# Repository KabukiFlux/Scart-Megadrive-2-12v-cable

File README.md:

# Megadrive/Genesis 2 to Scart adapter with 12V

<b align="center">PCB form Megadrive/Genesis 2 RGB minidin to Scart adapter with 12V DCDC boost (4:3 switching)</b>

## Table of contents

- [Why](#why)
- [Description](#description)
- [Schematics](#schematics)
- [Install](#install)
- [Pics and final result](#pics-and-final-result)
- [Premade cables with minidin 9](#premade-cables-with-minidin-9)

## Why?

When we plug a Megadrive 2 console via scart on the "newer" CRT TVs as the minidin provides 5v on the console side the
tv will switch to AV with a 16:9 aspect ratio. We need to deliver between 9v to 12v on the swtiching side to output
directly to AV with 4:3 aspect ratio.

## Description

This is intended to be a PCB using the default Megadrive/Genesis 2 RGB cable schematic but adding the 12v DC-DC switching boost
on the scart side from the 5v supplied by the MD2.

This board intends to provide a standard Sega Megadrive 2 RGB cable (Sega Genesis).

In the BOM directory there's an interactive BOM with all the required components.

In the gerbers directory we have the gerbers to manufacture the boards.

In the KiCAD folder we can find the KiCAD project itself.

## Schematics

You can find a copy on PDF on the root of the repository.

## Install

1- Send to manufacture the GERBER board to JLCPCB or other PCB manufacturer.

2- Get the components required, you can see here the Bill Of Materials [BOM](ibom.html)

3- Solder the wire to each of the pads and to the scart male.

4- Remember to solder the shield of the scart to the GND as well to avoid noise issues.

### Pics and final result

At this stage you should have something like this:

## Premade cables with minidin 9

Of course you can always try to solder the minidin 9 connectors from Aliexpress, good luck with that!

(You will need good flux and scratch the surface - some of them are almost imposible)

But my recommendation is to buy these ones:

1- RS 75ohm cable with shield: [RS Spain link code 724-1150](https://es.rs-online.com/web/p/cables-din/7241150)

2- Minidin 9 male to male cable: [Aliexpress 3m male to male with shield](https://es.aliexpress.com/item/1005006201886253.html)

I'm not responsible
============
And yes, read below, no responsibility taken on bad use.

DISCLAIMER (See Licensing)
==========================
See LICENSE for more information.

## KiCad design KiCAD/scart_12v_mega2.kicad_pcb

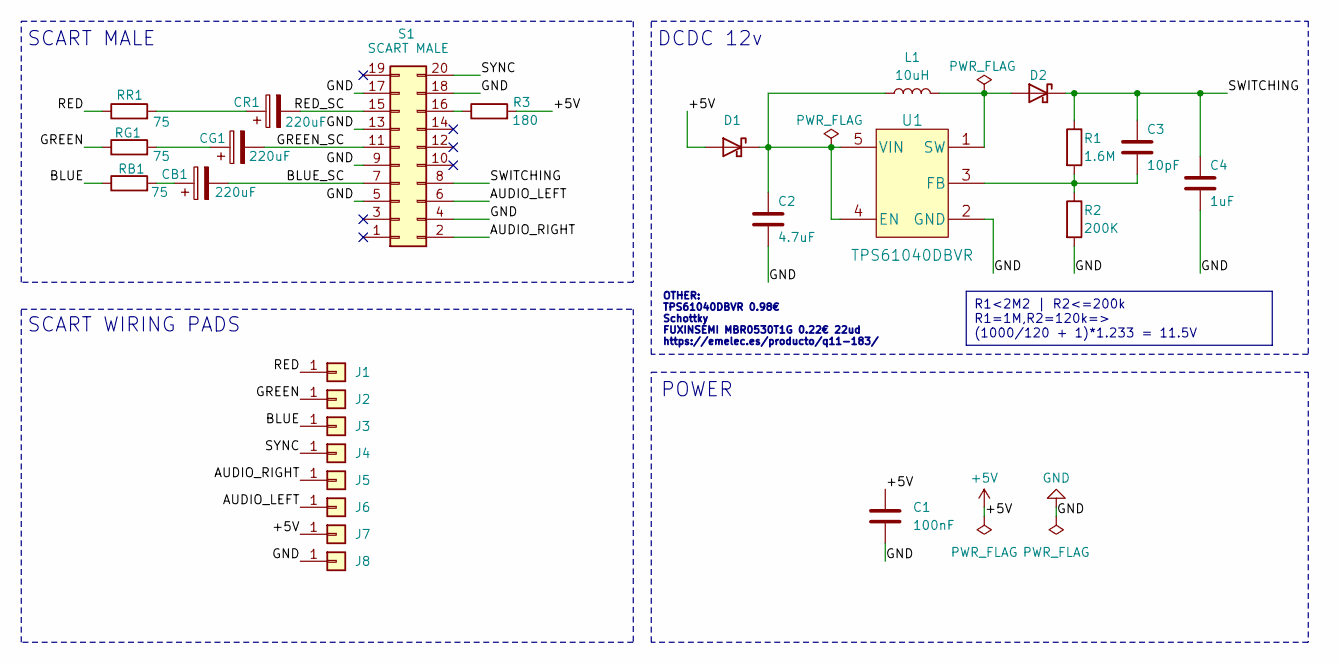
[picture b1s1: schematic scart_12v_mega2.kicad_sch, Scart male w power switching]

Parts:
C1: 100nF; C_0402_1005Metric; Manufacturer_Part_Number CL05B104KO5NNNC; LCSC Part C1525
C2: 4.7uF; C_0402_1005Metric; Manufacturer_Part_Number CL05A475MP5NRNC; LCSC Part C23733
C3: 10pF; C_0402_1005Metric; Manufacturer_Part_Number CL05C100JB5NNNC; LCSC Part C32949
C4: 1uF; C_0402_1005Metric; Manufacturer_Part_Number CL05A105KA5NQNC; LCSC Part C52923
CB1: 220uF; CP_EIA-3528-21_Kemet-B_Pad1.50x2.35mm_HandSolder; Manufacturer_Part_Number T520B227M006ATE045; LCSC Part C254404
CG1: 220uF; CP_EIA-3528-21_Kemet-B_Pad1.50x2.35mm_HandSolder; Manufacturer_Part_Number T520B227M006ATE045; LCSC Part C254404
CR1: 220uF; CP_EIA-3528-21_Kemet-B_Pad1.50x2.35mm_HandSolder; Manufacturer_Part_Number T520B227M006ATE045; LCSC Part C254404
D1, D2: D_Schottky; D_SOD-323_HandSoldering; Manufacturer_Part_Number 1N5819WS; LCSC Part C191023
J1, J2, J3, J4, J5, J6, J7: Conn_01x01; PAD2x2mm
J8: Conn_01x01; PAD2x8mm
L1: 10uH; L_0603_1608Metric; Manufacturer_Part_Number MLZ1608M100WTD25; LCSC Part C2047264
R1: 1.6M; R_0402_1005Metric; Manufacturer_Part_Number RC0402FR-071M6L; LCSC Part C327245
R2: 200K; R_0402_1005Metric; Manufacturer_Part_Number 0402WGF2003TCE; LCSC Part C25764
R3: 180; R_0402_1005Metric; Manufacturer_Part_Number 0402WGF1800TCE; LCSC Part C38941
RB1: 75; R_0603_1608Metric; Manufacturer_Part_Number 0603WAF750JT5E; LCSC Part C4275
RG1: 75; R_0603_1608Metric; Manufacturer_Part_Number 0603WAF750JT5E; LCSC Part C4275
RR1: 75; R_0603_1608Metric; Manufacturer_Part_Number 0603WAF750JT5E; LCSC Part C4275
S1: SCART MALE; SCART
U1: TPS61040DBVR; SOT-23-5_HandSoldering; Manufacturer_Part_Number TPS61040DBVR; LCSC Part C7722

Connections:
+5V: C1.1, D1.2 (A), J7.1, R3.2
/AUDIO_LEFT: J6.1, S1.6
/AUDIO_RIGHT: J5.1, S1.2
/BLUE: J3.1, RB1.1
/BLUE_SC: CB1.2, S1.7
/GREEN: J2.1, RG1.1
/GREEN_SC: CG1.2, S1.11
/RED: J1.1, RR1.1
/RED_SC: CR1.2, S1.15
/SWITCHING: C3.1, C4.1, D2.1 (K), R1.1, S1.8
/SYNC: J4.1, S1.20
GND: C1.2, C2.2, C4.2, J8.1, R2.2, S1.4, S1.5, S1.9, S1.13, S1.17, S1.18, U1.2 (GND)
unnamed: CB1.1, RB1.2
unnamed: CG1.1, RG1.2
unnamed: CR1.1, RR1.2
unnamed: C2.1, D1.1 (K), L1.1, U1.4 (EN), U1.5 (VIN)
unnamed: D2.2 (A), L1.2, U1.1 (SW)
unnamed: R3.1, S1.16
unnamed: C3.2, R1.2, R2.1, U1.3 (FB)

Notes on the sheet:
R1<2M2 | R2<=200k R1=1M,R2=120k=> (1000/120 + 1)*1.233 = 11.5V
OTHER: TPS61040DBVR 0.98€ Schottky FUXINSEMI MBR0530T1G 0.22€ 22ud https://emelec.es/producto/q11-183/
SCART WIRING PADS
POWER
SCART MALE
DCDC 12v

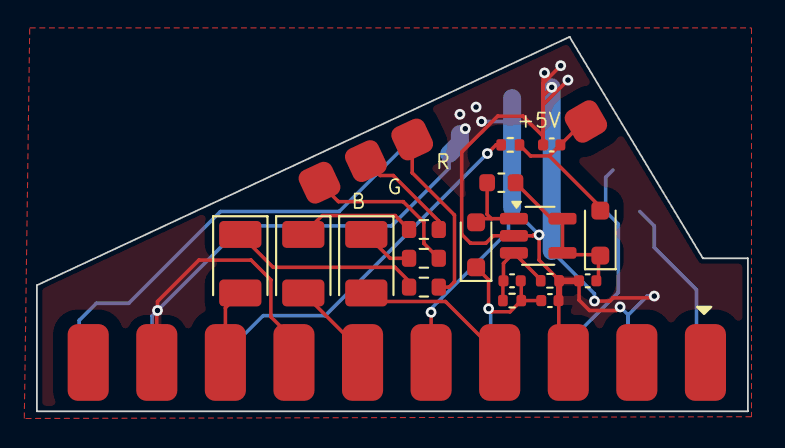
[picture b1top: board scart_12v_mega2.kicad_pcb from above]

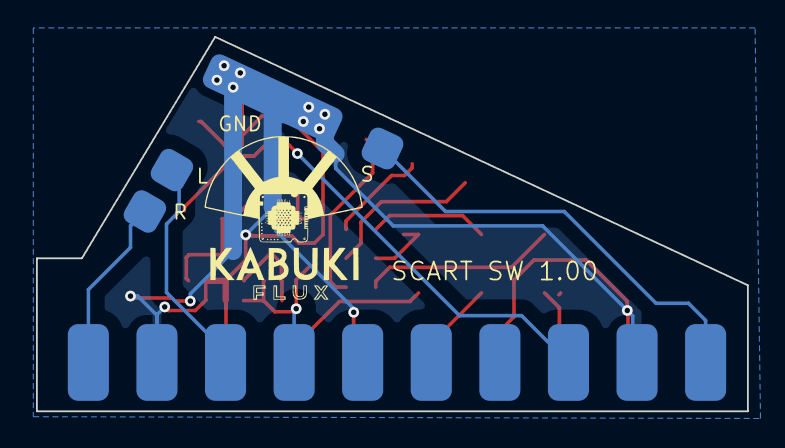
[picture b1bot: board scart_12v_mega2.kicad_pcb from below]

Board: 2 copper layers, 39.5 x 20.8 mm, 27 parts (5 on the bottom side), 19 nets.

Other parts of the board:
G1: LOGO; LogoKabuki_10mm

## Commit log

2024-05-10 ScartMD2PCBcable
2024-05-16 Added bom csv and removed from gitignore list
